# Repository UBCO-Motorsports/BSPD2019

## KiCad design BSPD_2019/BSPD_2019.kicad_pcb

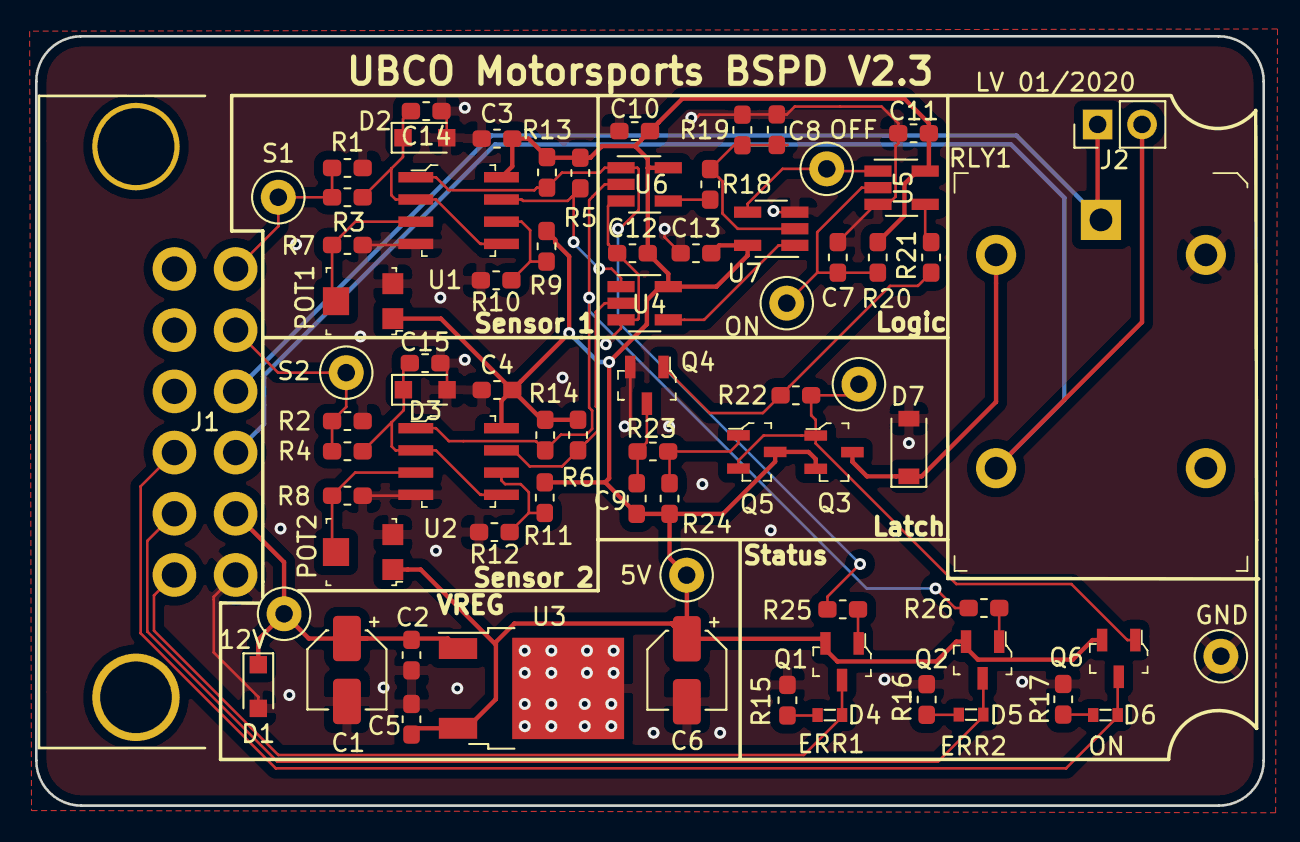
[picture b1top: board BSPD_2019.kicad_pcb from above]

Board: 2 copper layers, 70.2 x 44.0 mm, 74 parts (0 on the bottom side), 36 nets.

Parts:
C1, C6: 10u; CP_Elec_4x5.4
C2, C5: 10n; C_0603_1608Metric_Pad1.05x0.95mm_HandSolder
C3, C4, C10, C11, C12, C13, C14, C15: 100n; C_0603_1608Metric_Pad1.05x0.95mm_HandSolder
C7, C8: 22u; C_0603_1608Metric_Pad1.05x0.95mm_HandSolder
C9: 1u; C_0603_1608Metric_Pad1.05x0.95mm_HandSolder
D1: ESD; D_SOD-323_HandSoldering
D2, D3: TVS; D_SOD-323_HandSoldering
D4: LED_ERR1 (RED); 0603
D5: LED_ERR2 (RED); 0603
D6: LED_RELAYON (GREEN); 0603
D7: Flyback; D_SOD-123
J1: MX120G
J2: Override; PinHeader_1x02_P2.54mm_Vertical
POT1, POT2: 20k; Trimpot_3.8mmx3.6mm_TC33X-2-103E
Q1, Q2, Q3, Q6: BSS84; SOT-23-3
Q4: NPN; SOT-23-3
Q5: PNP; SOT-23-3
R1, R2, R9, R11, R19, R20: 100k; R_0603_1608Metric_Pad1.05x0.95mm_HandSolder
R3, R4, R5, R6, R7, R8, R10, R12, R13, R14, R21, R23, R24: 10k; R_0603_1608Metric_Pad1.05x0.95mm_HandSolder
R15, R16, R17: 220; R_0603_1608Metric_Pad1.05x0.95mm_HandSolder
R18: 70k; R_0603_1608Metric_Pad1.05x0.95mm_HandSolder
R22: 20k; R_0603_1608Metric_Pad1.05x0.95mm_HandSolder
R25, R26: 1k; R_0603_1608Metric_Pad1.05x0.95mm_HandSolder
RLY1: JSM1-12V-5; Relay_JSM1-12V-5
TP1: SENS1 TP; TestPoint_Loop_D2.50mm_Drill1.0mm_LowProfile
TP2: SENS2 TP; TestPoint_Loop_D2.50mm_Drill1.0mm_LowProfile
TP3: GND TP; TestPoint_Loop_D2.50mm_Drill1.0mm_LowProfile
TP4: 5V TP; TestPoint_Loop_D2.50mm_Drill1.0mm_LowProfile
TP5: 12V TP; TestPoint_Loop_D2.50mm_Drill1.0mm_LowProfile
TP6: Shutdown TP; TestPoint_Loop_D2.50mm_Drill1.0mm_LowProfile
TP7: Power-On TP; TestPoint_Loop_D2.50mm_Drill1.0mm_LowProfile
TP8: Latch TP; TestPoint_Loop_D2.50mm_Drill1.0mm_LowProfile
U1, U2: LM393ADR; SOIC-8_W3.9mm
U3: NCV7805BDTRKG; TO-252-3_TabPin4
U4: NAND GATE; SOT-23-5_HandSoldering
U5: AND; SOT-23-5_HandSoldering
U6: NOR GATE; SOT-23-5_HandSoldering
U7: OR GATE; SOT-23-5_HandSoldering

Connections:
+5V: C3.2, C4.2, C5.2, C6.1, C9.1, C10.2, C11.2, C12.2, C13.2, POT1.1, POT2.1, Q1.2, Q2.2, Q3.2, Q5.3, Q6.2, R5.2, R6.2, R9.2, R11.2, R13.2, R14.2, R20.1, R24.1, TP4.1, U1.8, U2.8, U3.3, U4.5, U5.5, U6.5, U7.5
+12V: C1.1, C2.2, D1.1, J1.5, TP5.1, U3.1
ERR1_OUT: D4.1, J1.12, Q1.3
ERR2_OUT: D5.1, J1.11, Q2.3
GND: C1.2, C2.1, C3.1, C4.1, C5.1, C6.2, C7.2, C8.2, C10.1, C11.1, C12.1, C13.1, C14.1, C15.1, D1.2, D2.2, D3.2, D7.2, J1.6, POT1.3, POT2.3, Q4.2, R1.1, R2.1, R7.1, R8.1, R10.1, R12.1, R15.1, R16.1, R17.1, R19.2, RLY1.5, TP3.1, U1.4, U2.4, U3.2, U3.4, U4.3, U5.3, U6.3, U7.3
unnamed: C7.1, R20.2, TP7.1, U5.2
unnamed: C8.1, R18.2, R19.1, U7.2
unnamed: C9.2, Q4.3, R23.2
unnamed: C14.2, D2.1, R3.1, U1.2, U1.5
unnamed: C15.2, D3.1, R4.1, U2.2, U2.5
unnamed: D4.2, R15.2
unnamed: D5.2, R16.2
unnamed: D6.2, R17.2
unnamed: POT1.2, R7.2, U1.3
unnamed: POT2.2, R8.2, U2.3
unnamed: Q1.1, R25.1
unnamed: Q2.1, R26.1
unnamed: Q4.1, R21.2, R22.1
unnamed: Q5.1, R23.1, R24.2
unnamed: R9.1, R10.2, U1.6
unnamed: R11.1, R12.2, U2.6
unnamed: R18.1, U6.4
unnamed: R21.1, U5.4
unnamed: TP6.1, U5.1, U7.4
unnamed: U4.4, U7.1
ON_OUT: D6.1, J1.10, Q6.3
RELAY: Q3.1, Q5.2, Q6.1, R22.2, TP8.1
RELAY_I: J1.3, J2.1, RLY1.1
RELAY_O: J1.4, J2.2, RLY1.3
Relay_Supply: D7.1, Q3.3, RLY1.2
SENS1: J1.1, R1.2, R3.2, TP1.1
SENS1_DC: R5.1, U1.7, U4.1
SENS1_ERR: R13.1, R25.2, U1.1, U6.1
SENS2: J1.2, R2.2, R4.2, TP2.1
SENS2_DC: R6.1, U2.7, U4.2
SENS2_ERR: R14.1, R26.2, U2.1, U6.2

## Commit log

2019-11-20 First Add
2019-11-29 Increased LED resistors from 100 to 220ohms
2019-12-03 Fixed ESD diode footprints
2020-01-16 V2.2
    Modifications to logic replacing the previous multi-diode layout to a logical OR gate. Changed VREG to a novalithic part with a different footprint
2021-01-28 Some small changes
2021-01-28 Updated symbols to use Lukas_Library
